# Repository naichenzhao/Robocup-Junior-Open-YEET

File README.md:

**Robocup Junior YEET**

These are the robot designs I created for Robocup Junior Open weight. 

These are my own creations and since I have graduated from the event, anyone rteading this is free to build off of any of my designs. My hope for this is to inspire others to build off of what I haev and use them to create even better concepts for the competition.

If you have any questions or concerns regarding the design, feel free to contact me:
- Twitter: https://twitter.com/N_zhao_
- Discord: https://discord.gg/ySBR4mmBkV

Included in the repo are:
- My 2020 design I planned on using for that year's competition - This is mostly tested but never created
- My 2021 design Which is pureley theoretical. It is a modefied version of the 2020 design built around a 20cm diameter

**2020 Design:**
This is the robot I planned on using for the 2020 competition (Which was cancelled due to covid). Some parts of the robot were tested but it was never completed as production stopped when the competition was cancelled

The specs of the robot are:
- 2x Teensy 4.0
- 1x Teensy 3.5
- 1x Open MV H7 (Omnidirectional mirror)
- 1x Spinning LIDAR
- 1x Bluetooth module
- 1x BNO-055 Accelerometer
- 2x Dribbler
- 2x Directional Kicker (I created models using both slider and geneva methods)
- 32x Photoresistors w/ LEDs (Controlled by 2 multiplexers)
- 12x Buttons w/ LEDs
- 2x IR laser module

**2021 Design:**
This is a robot built for the 2021 competition but since there is a significant chance that the competition will be cancalled, I have decided to thus release all of the robot files. This design is a smaller version built around the 2020 design created around a 20cm diameter instead of a 22 cm diameter

The specs of the robot are:
- 2x Teensy 4.0
- 1x Teensy 4.1
- 1x Open MV H7 (Omnidirectional mirror)
- 1x Spinning LIDAR
- 1x Bluetooth module
- 1x BNO-055 Accelerometer
- 2x Dribbler
- 2x Kicker
- 32x Photoresistors w/ LEDs (Controlled by 2 multiplexers)
- 8x Buttons w/ LEDs (Intead of individual LEDs, I am using a neopixel strip to conserve pins)
- 2x IR laser module

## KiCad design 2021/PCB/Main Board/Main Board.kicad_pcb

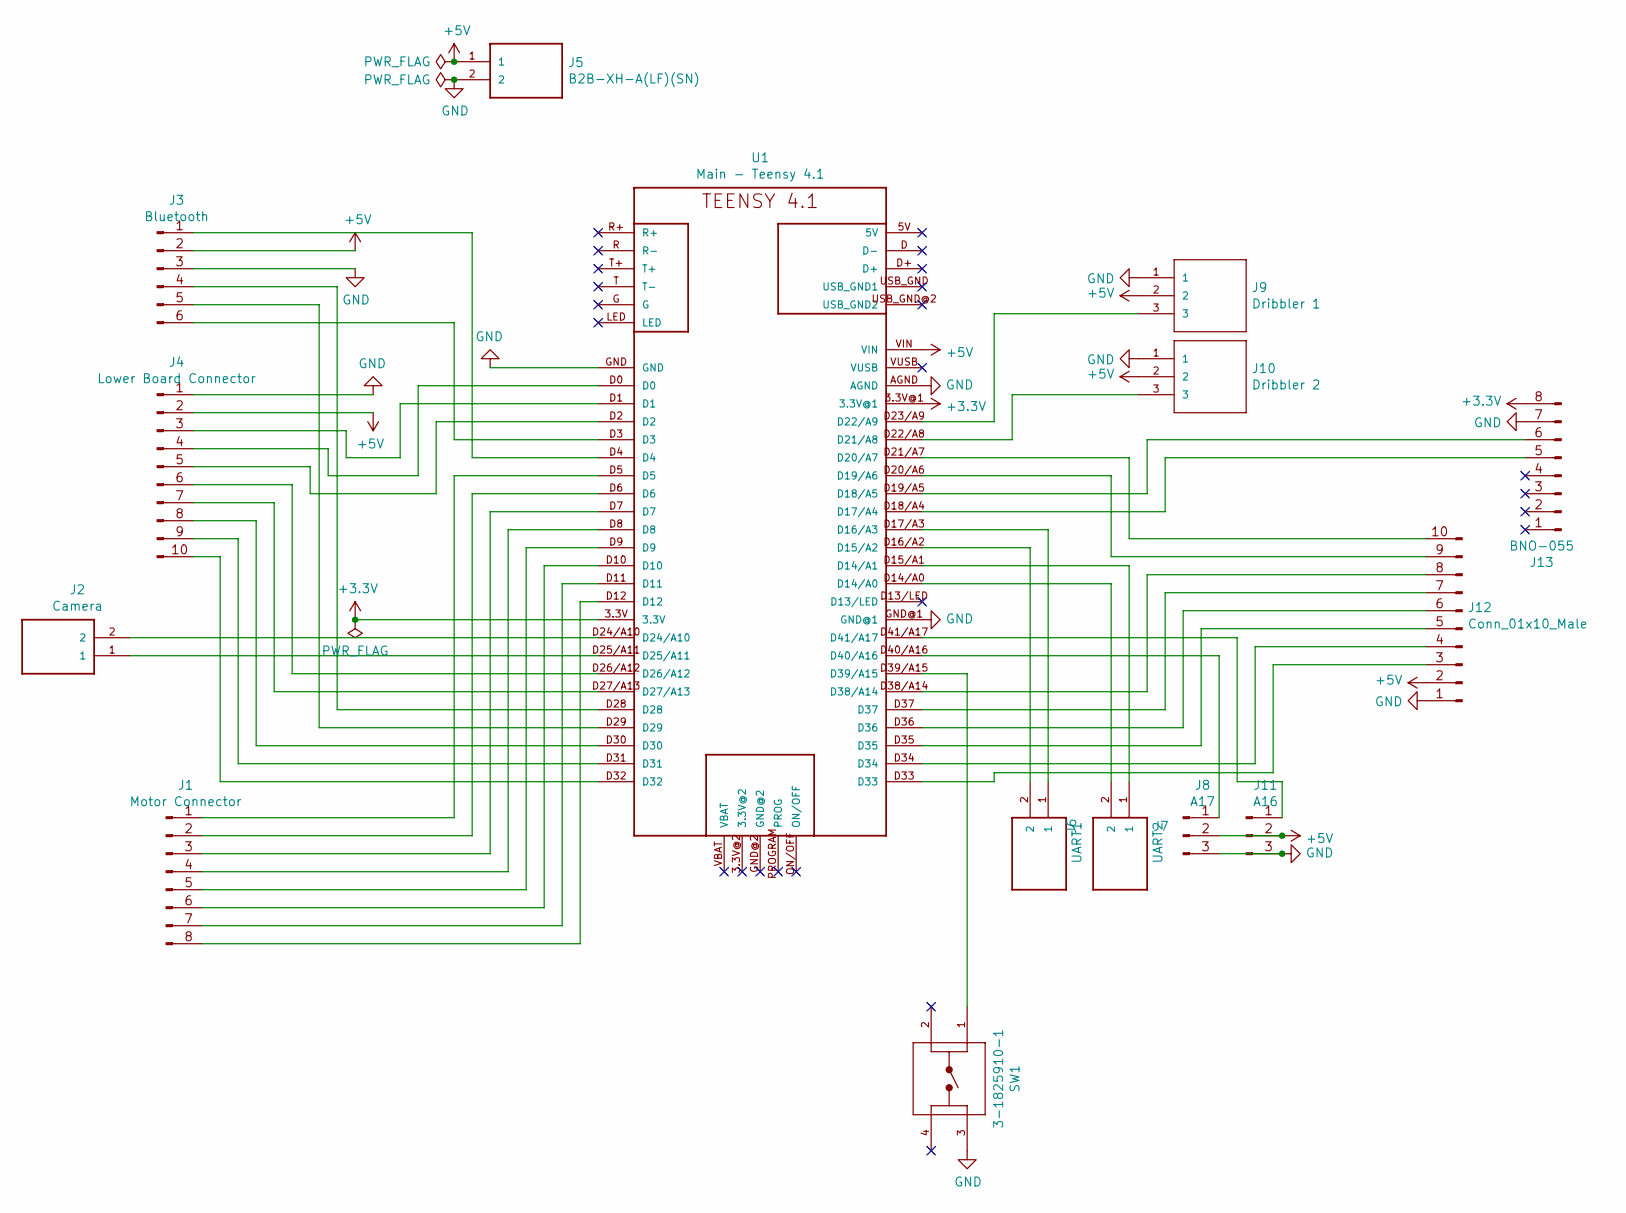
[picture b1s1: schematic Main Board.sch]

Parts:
J1: Motor Connector; Stocko_MKS_1658-6-0-808_1x8_P2.50mm_Vertical
J2: Camera; JST_EH_B2B-EH-A_1x02_P2.50mm_Vertical
J3: Bluetooth; Stocko_MKS_1656-6-0-606_1x6_P2.50mm_Vertical
J4: Lower Board Connector; JST_XH_B10B-XH-AM_1x10_P2.50mm_Vertical
J5: B2B-XH-A(LF)(SN); JST_EH_B2B-EH-A_1x02_P2.50mm_Vertical
J6: UART1; JST_EH_B2B-EH-A_1x02_P2.50mm_Vertical
J7: UART2; JST_EH_B2B-EH-A_1x02_P2.50mm_Vertical
J8: A17; JST_EH_B3B-EH-A_1x03_P2.50mm_Vertical
J9: Dribbler 1; JST_EH_B3B-EH-A_1x03_P2.50mm_Vertical
J10: Dribbler 2; JST_EH_B3B-EH-A_1x03_P2.50mm_Vertical
J11: A16; JST_EH_B3B-EH-A_1x03_P2.50mm_Vertical
J12: Conn_01x10_Male; JST_XH_B10B-XH-AM_1x10_P2.50mm_Vertical
J13: BNO-055; PinHeader_1x08_P2.54mm_Vertical
SW1: 3-1825910-1; TE_3-1825910-1
U1: Main - Teensy 4.1; DEV-16771

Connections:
+3V3: J13.8, U1.3.3V, U1.3.3V@1
+5V: J3.2, J4.2, J5.1, J8.2, J9.2, J10.2, J11.2, J12.2, U1.VIN
GND: J3.3, J4.1, J5.2, J8.3, J9.1, J10.1, J11.3, J12.1, J13.7, SW1.3, U1.AGND, U1.GND, U1.GND@1
unnamed: J1.1, U1.D5
unnamed: J1.2, U1.D6
unnamed: J1.3, U1.D7
unnamed: J1.4, U1.D8
unnamed: J1.5, U1.D9
unnamed: J1.6, U1.D10
unnamed: J1.7, U1.D11
unnamed: J1.8, U1.D12
unnamed: J2.1, U1.D25/A11
unnamed: J2.2, U1.D24/A10
unnamed: J3.1, U1.D4
unnamed: J3.4, U1.D28
unnamed: J3.5, U1.D29
unnamed: J3.6, U1.D3
unnamed: J4.3, U1.D1
unnamed: J4.4, U1.D0
unnamed: J4.5, U1.D2
unnamed: J4.6, U1.D26/A12
unnamed: J4.7, U1.D27/A13
unnamed: J4.8, U1.D30
unnamed: J4.9, U1.D31
unnamed: J4.10, U1.D32
unnamed: J6.1, U1.D17/A3 (D16/A3)
unnamed: J6.2, U1.D16/A2 (D15/A2)
unnamed: J7.1, U1.D15/A1 (D14/A1)
unnamed: J7.2, U1.D14/A0
unnamed: J8.1, U1.D40/A16
unnamed: J9.3, U1.D23/A9 (D22/A9)
unnamed: J10.3, U1.D22/A8 (D21/A8)
unnamed: J11.1, U1.D41/A17
unnamed: J12.3, U1.D33
unnamed: J12.4, U1.D34
unnamed: J12.5, U1.D35
unnamed: J12.6, U1.D36
unnamed: J12.7, U1.D37
unnamed: J12.8, U1.D38/A14
unnamed: J12.9, U1.D20/A6 (D19/A6)
unnamed: J12.10, U1.D21/A7 (D20/A7)
unnamed: J13.5, U1.D18/A4 (D17/A4)
unnamed: J13.6, U1.D19/A5 (D18/A5)
unnamed: SW1.1, U1.D39/A15

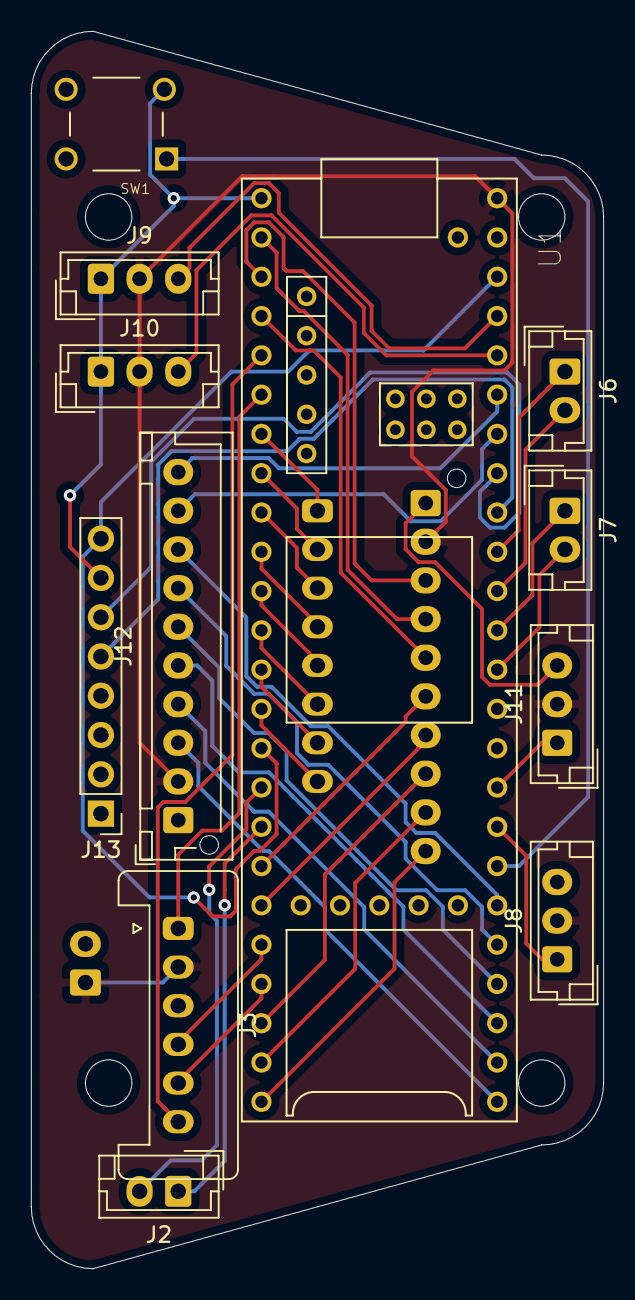
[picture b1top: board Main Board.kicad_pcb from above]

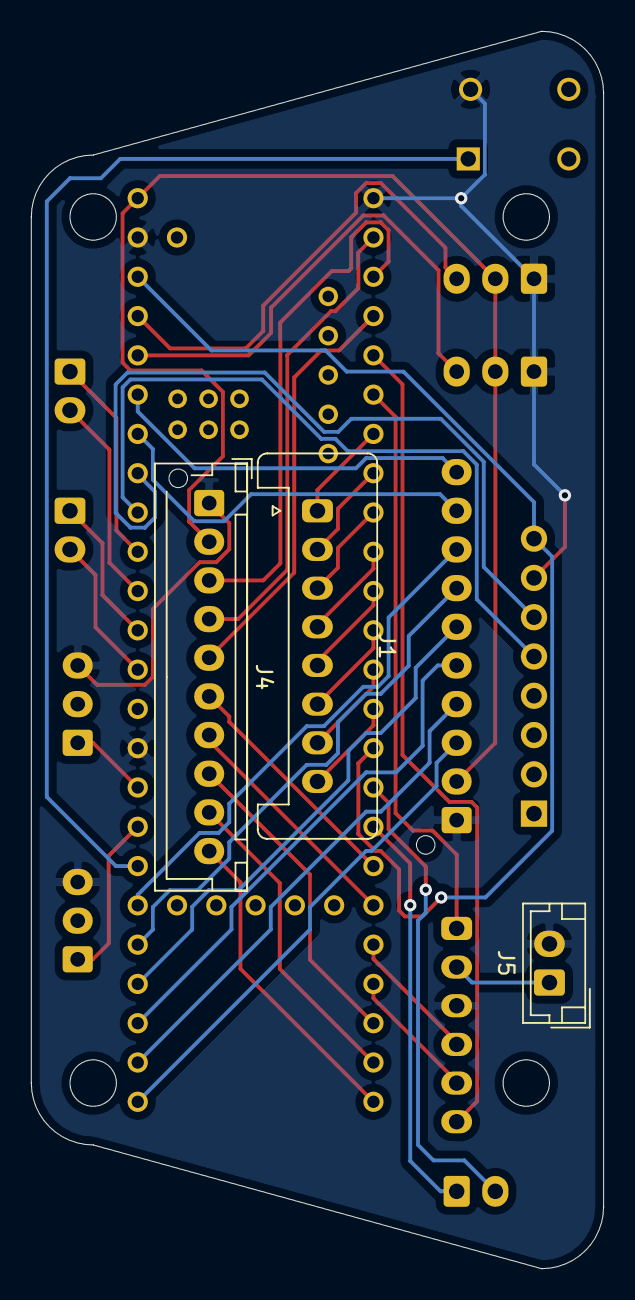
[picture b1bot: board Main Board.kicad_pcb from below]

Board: 2 copper layers, 37.0 x 80.0 mm, 15 parts (3 on the bottom side), 44 nets.

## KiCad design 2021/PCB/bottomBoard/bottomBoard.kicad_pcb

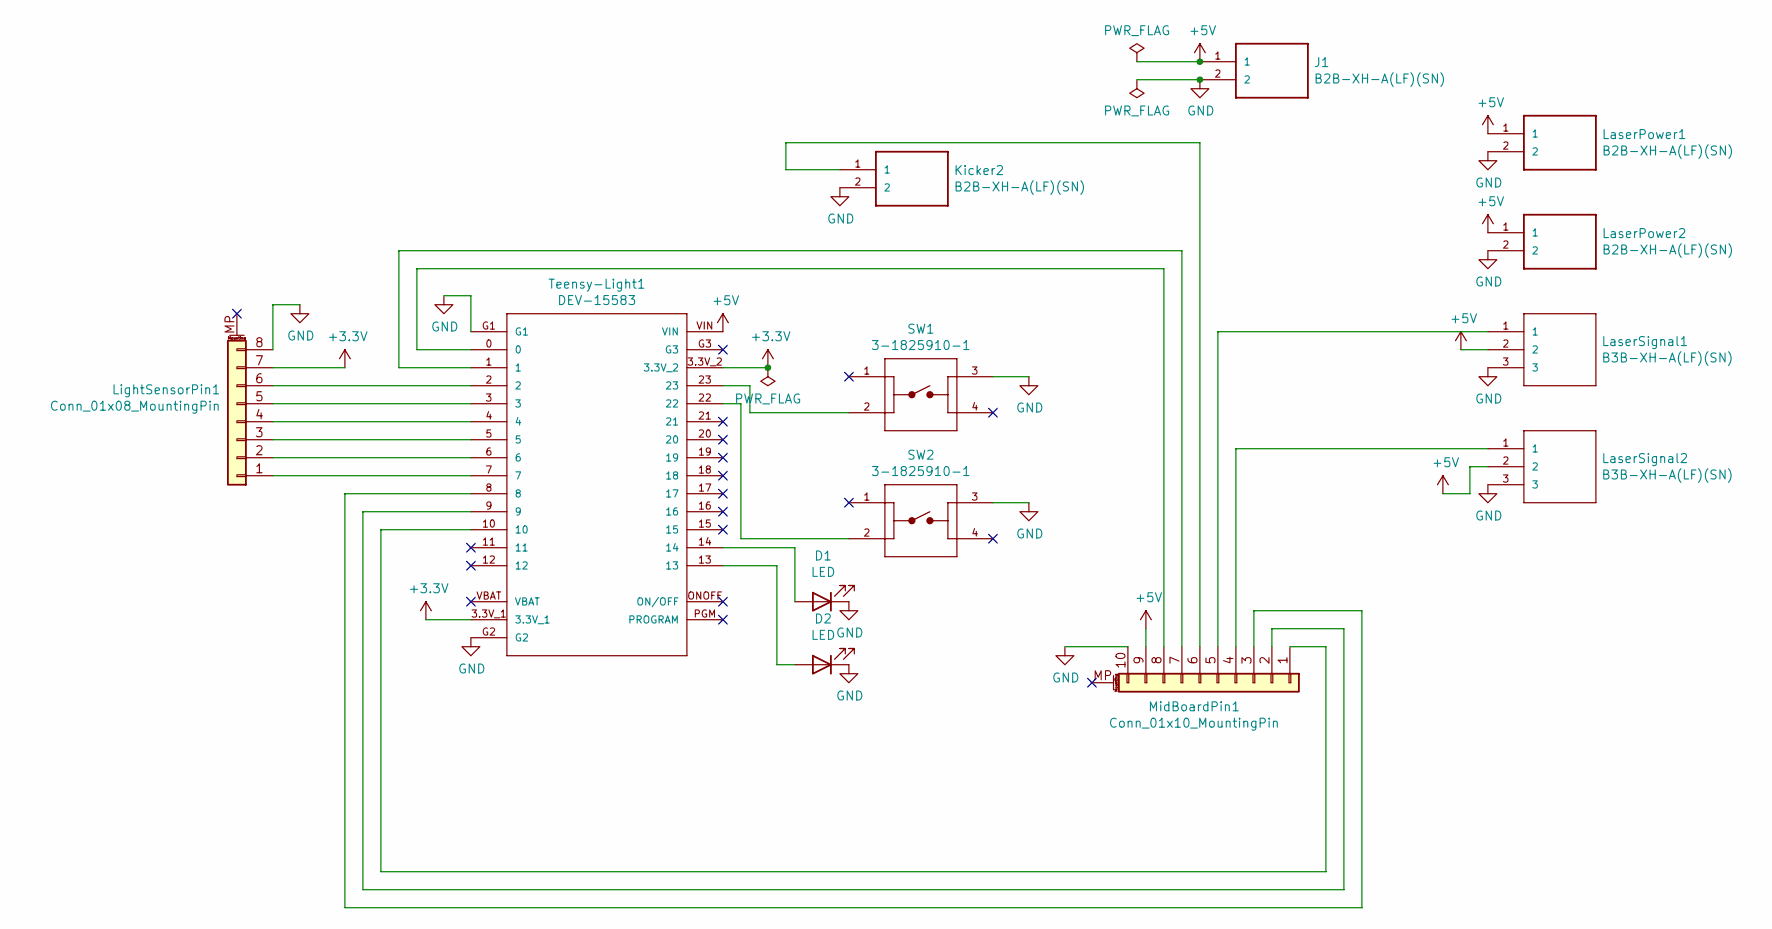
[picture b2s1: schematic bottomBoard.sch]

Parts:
D1, D2: LED; C_1206_3216Metric
J1: B2B-XH-A(LF)(SN); JST_B2B-XH-A(LF)(SN)
Kicker2: B2B-XH-A(LF)(SN); JST_B2B-XH-A(LF)(SN)
LaserPower1, LaserPower2: B2B-XH-A(LF)(SN); JST_B2B-XH-A(LF)(SN)
LaserSignal1, LaserSignal2: B3B-XH-A(LF)(SN); JST_B3B-XH-A(LF)(SN)
LightSensorPin1: Conn_01x08_MountingPin; PinHeader_1x08_P2.54mm_Vertical
MidBoardPin1: Conn_01x10_MountingPin; PinHeader_1x10_P2.54mm_Vertical
SW1, SW2: 3-1825910-1; TE_3-1825910-1
Teensy-Light1: DEV-15583; MODULE_DEV-15583

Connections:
+3V3: LightSensorPin1.7, Teensy-Light1.3.3V_1, Teensy-Light1.3.3V_2
+5V: J1.1, LaserPower1.1, LaserPower2.1, LaserSignal1.2, LaserSignal2.2, MidBoardPin1.9, Teensy-Light1.VIN
GND: D1.1 (K), D2.1 (K), J1.2, Kicker2.2, LaserPower1.2, LaserPower2.2, LaserSignal1.3, LaserSignal2.3, LightSensorPin1.8, MidBoardPin1.10, SW1.3, SW2.3, Teensy-Light1.G1, Teensy-Light1.G2
unnamed: D1.2 (A), Teensy-Light1.14
unnamed: D2.2 (A), Teensy-Light1.13
unnamed: Kicker2.1, MidBoardPin1.6
unnamed: LaserSignal1.1, MidBoardPin1.5
unnamed: LaserSignal2.1, MidBoardPin1.4
unnamed: LightSensorPin1.1, Teensy-Light1.7
unnamed: LightSensorPin1.2, Teensy-Light1.6
unnamed: LightSensorPin1.3, Teensy-Light1.5
unnamed: LightSensorPin1.4, Teensy-Light1.4
unnamed: LightSensorPin1.5, Teensy-Light1.3
unnamed: LightSensorPin1.6, Teensy-Light1.2
unnamed: MidBoardPin1.1, Teensy-Light1.10
unnamed: MidBoardPin1.2, Teensy-Light1.9
unnamed: MidBoardPin1.3, Teensy-Light1.8
unnamed: MidBoardPin1.7, Teensy-Light1.1
unnamed: MidBoardPin1.8, Teensy-Light1.0
unnamed: SW1.2, Teensy-Light1.23
unnamed: SW2.2, Teensy-Light1.22

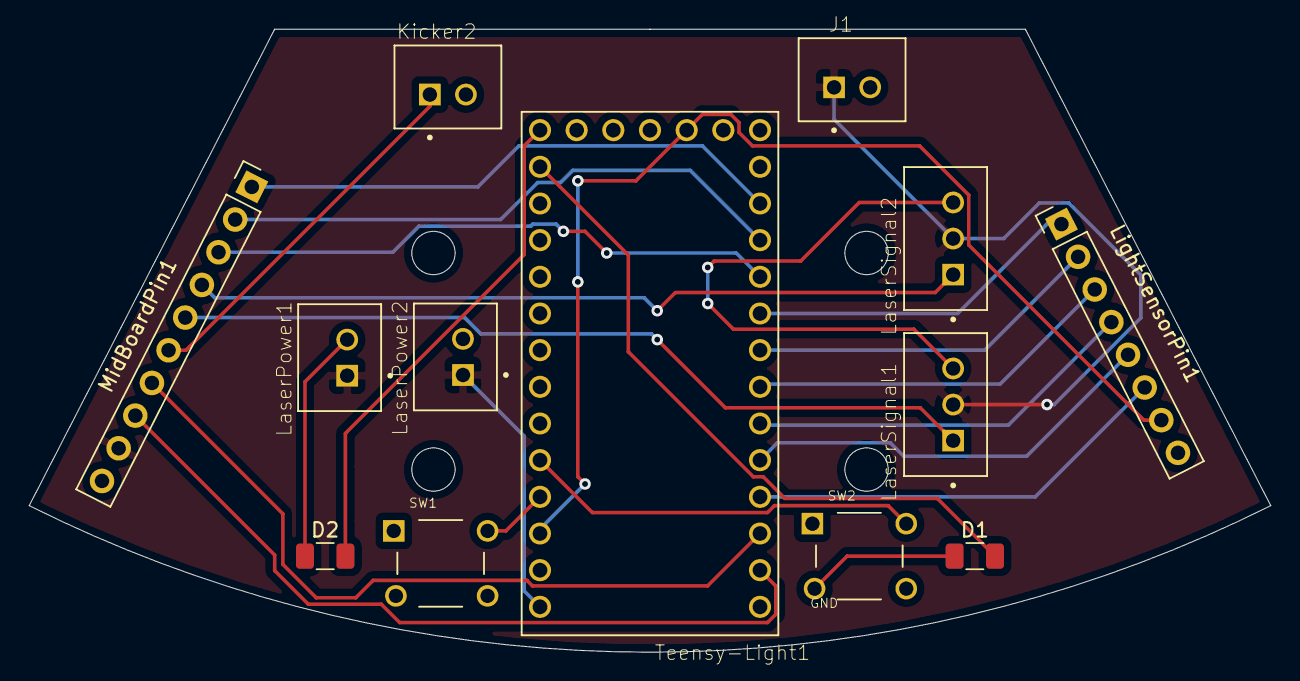
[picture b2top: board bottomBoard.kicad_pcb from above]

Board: 2 copper layers, 86.0 x 43.2 mm, 13 parts (0 on the bottom side), 21 nets.

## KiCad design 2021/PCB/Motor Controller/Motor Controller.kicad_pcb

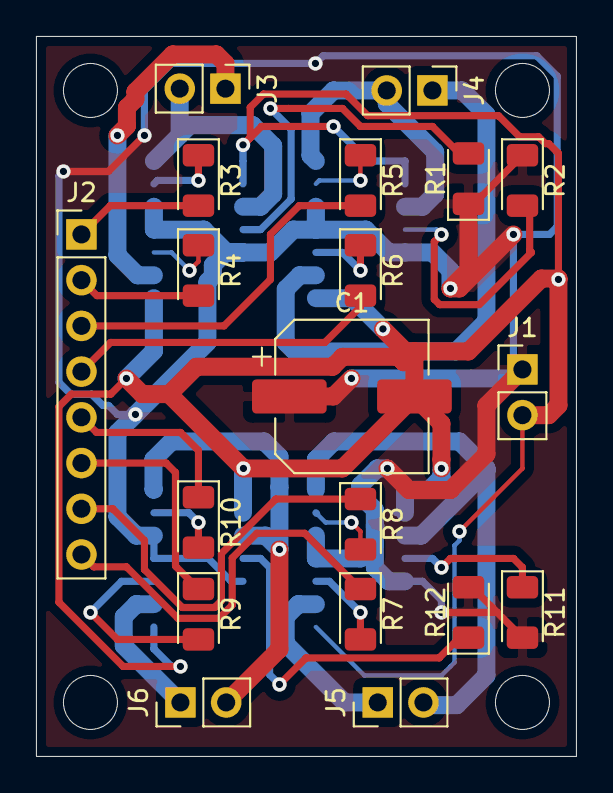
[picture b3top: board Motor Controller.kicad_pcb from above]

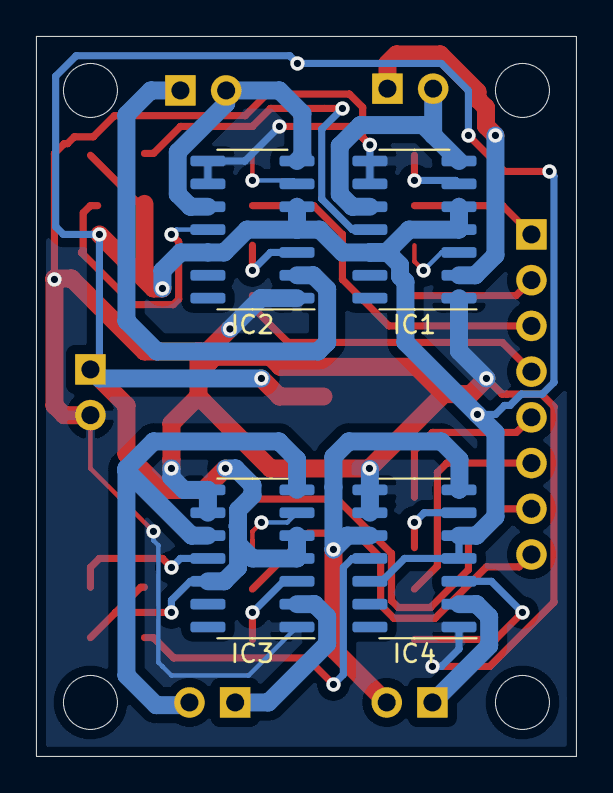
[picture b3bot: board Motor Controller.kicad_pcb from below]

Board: 2 copper layers, 30.0 x 40.0 mm, 23 parts (4 on the bottom side), 30 nets.

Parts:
C1: UUD1V331MNL1GS; CP_Elec_8x11.9
IC1, IC2, IC3, IC4: VNH7070ASTR; SOIC-14_3.9x8.7mm_P1.27mm
J1, J3, J4, J5, J6: Conn_01x02; PinHeader_1x02_P2.54mm_Vertical
J2: Conn_01x08_MountingPin; PinHeader_1x08_P2.54mm_Vertical
R1, R2, R3, R4, R5, R6, R7, R8, R9, R10, R11, R12: R_US; D_1206_3216Metric

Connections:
+12V: C1.1, IC1.4, IC1.5, IC1.12, IC2.4, IC2.5, IC2.12, IC3.4, IC3.5, IC3.12, IC4.4, IC4.5, IC4.12, J1.1, R1.1, R2.1, R11.2, R12.2
GND: C1.2, IC1.1, IC1.8, IC1.9, IC2.1, IC2.8, IC2.9, IC3.1, IC3.8, IC3.9, IC4.1, IC4.8, IC4.9, J1.2
unnamed: IC1.3, R4.1
unnamed: IC1.6, R3.1
unnamed: IC1.7, IC1.10, J3.2
unnamed: IC1.11, R1.2
unnamed: IC1.2, J3.1
unnamed: IC2.3, R6.1
unnamed: IC2.6, R5.1
unnamed: IC2.7, IC2.10, J4.2
unnamed: IC2.11, R2.2
unnamed: IC2.2, J4.1
unnamed: IC3.3, R7.2
unnamed: IC3.6, R8.2
unnamed: IC3.7, IC3.10, J5.2
unnamed: IC3.11, R11.1
unnamed: IC3.2, J5.1
unnamed: IC4.3, R9.2
unnamed: IC4.6, R10.2
unnamed: IC4.7, IC4.10, J6.2
unnamed: IC4.11, R12.1
unnamed: IC4.2, J6.1
unnamed: J2.1, R3.2
unnamed: J2.2, R4.2
unnamed: J2.3, R5.2
unnamed: J2.4, R6.2
unnamed: J2.5, R10.1
unnamed: J2.6, R9.1
unnamed: J2.7, R8.1
unnamed: J2.8, R7.1

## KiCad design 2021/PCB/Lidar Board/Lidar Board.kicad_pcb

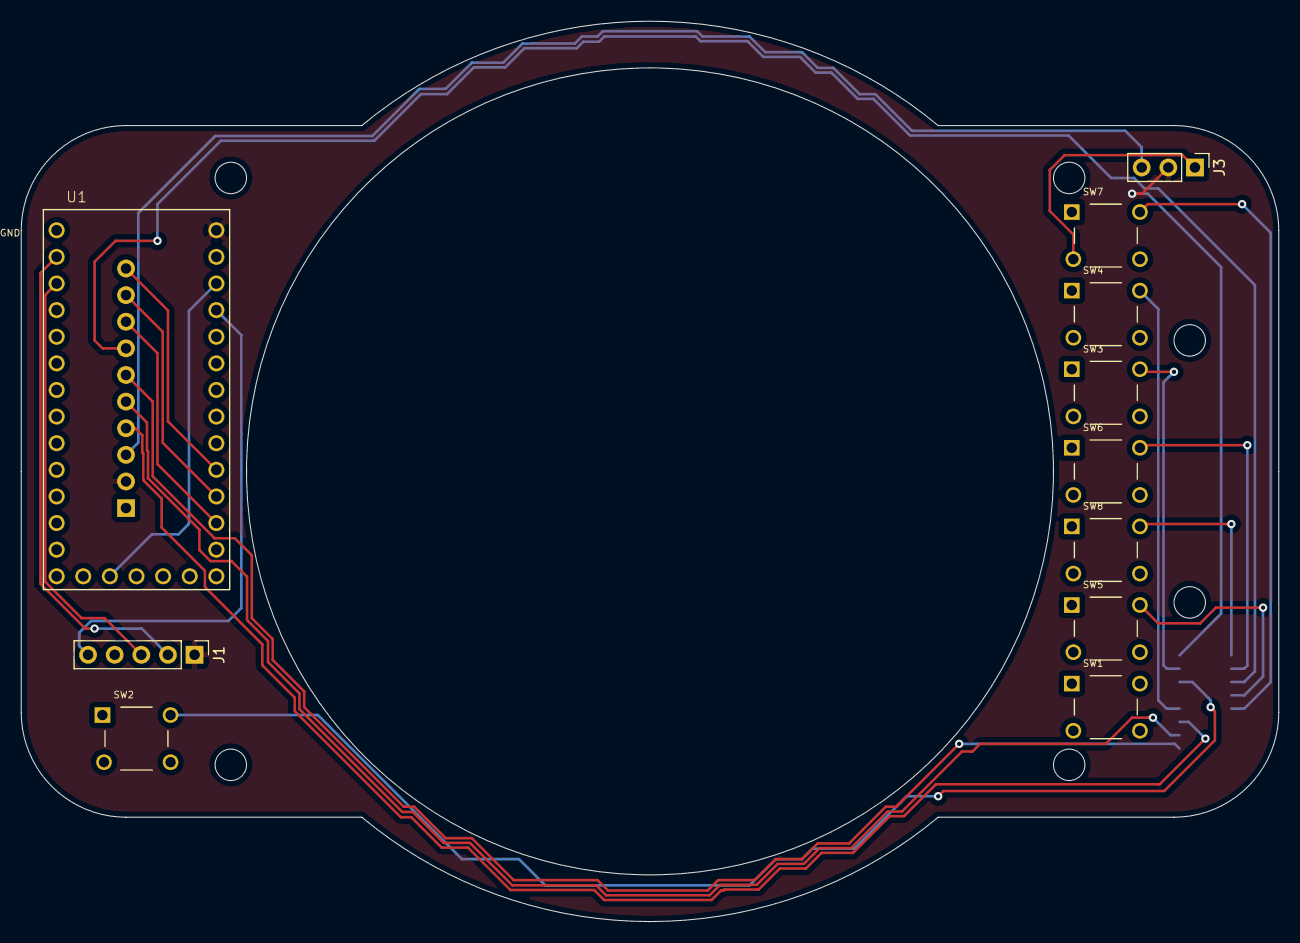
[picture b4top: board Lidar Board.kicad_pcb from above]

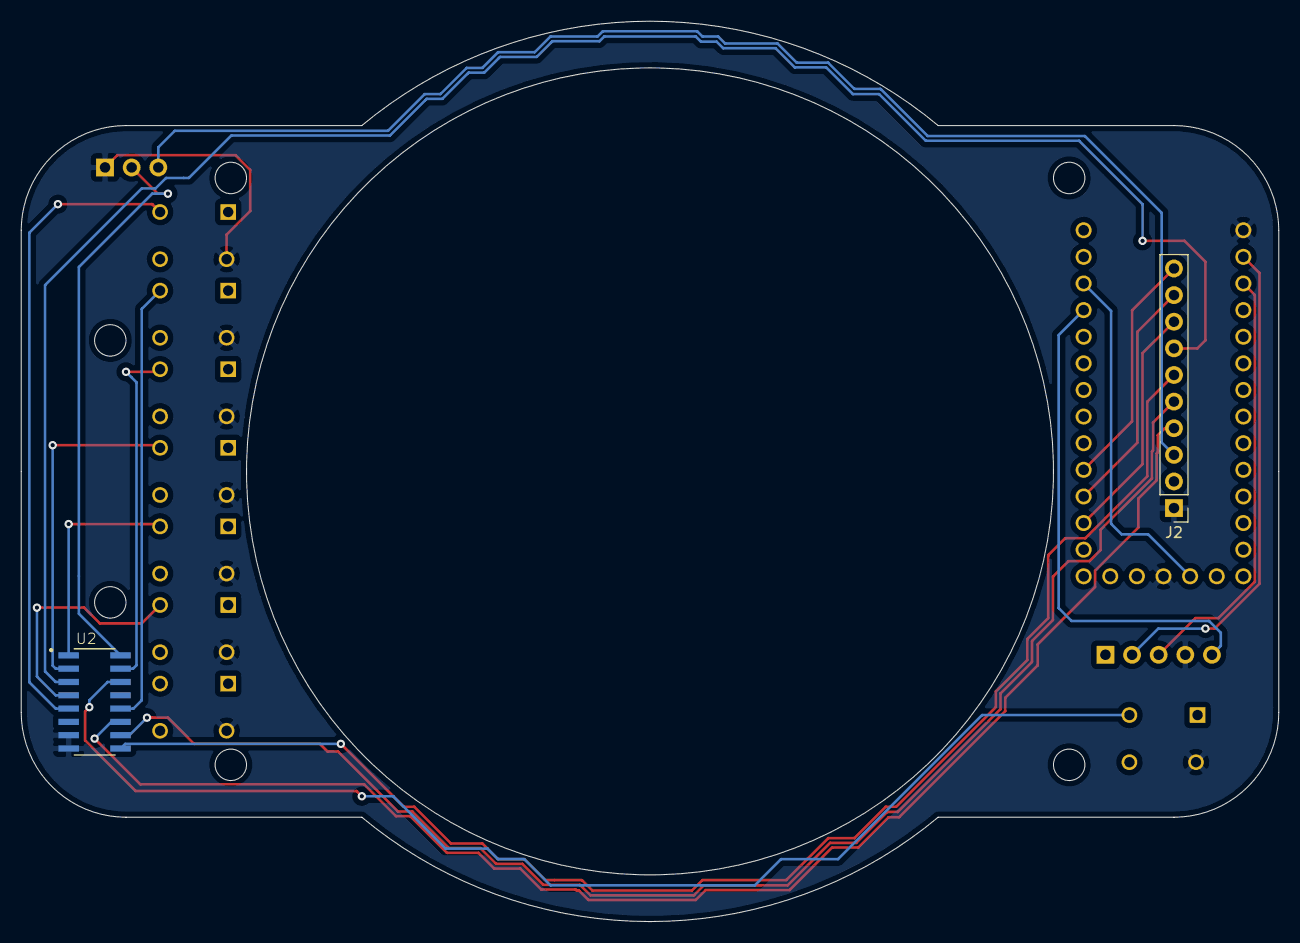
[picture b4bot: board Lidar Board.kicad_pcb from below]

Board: 2 copper layers, 120.0 x 85.9 mm, 13 parts (2 on the bottom side), 21 nets.

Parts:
J1: Conn_01x05_Male; PinHeader_1x05_P2.54mm_Vertical
J2: Conn_01x10_Male; PinHeader_1x10_P2.54mm_Vertical
J3: Conn_01x03_Male; PinHeader_1x03_P2.54mm_Vertical
SW1, SW2, SW3, SW4, SW5, SW6, SW7, SW8: 3-1825910-1; TE_3-1825910-1
U1: DEV-15583; MODULE_DEV-15583
U2: SN74LV4051ADR; SOIC127P600X175-16N

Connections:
+3V3: U1.3.3V_1, U1.3.3V_2
+5V: J1.1, J2.2, J3.2, U1.VIN, U2.16
GND: J1.4, J2.1, J3.1, SW1.3, SW2.3, SW3.3, SW4.3, SW5.3, SW6.3, SW7.3, SW8.3, U1.G1, U1.G2, U2.7, U2.8
unnamed: J1.2, U1.0
unnamed: J1.3, U1.1
unnamed: J1.5, U1.23
unnamed: J2.3, J3.3
unnamed: J2.4, U2.11
unnamed: J2.5, U2.10
unnamed: J2.6, U2.9
unnamed: J2.7, U2.3
unnamed: J2.8, U1.15
unnamed: J2.9, U1.16
unnamed: J2.10, U1.17
unnamed: SW2.2, U2.14
unnamed: SW3.2, U2.15
unnamed: SW4.2, U2.12
unnamed: SW5.2, U2.4
unnamed: SW6.2, U2.2
unnamed: SW7.2, U2.5
unnamed: SW8.2, U2.1

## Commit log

2021-05-24 added files poggers
2021-05-24 added links to readme
2021-05-24 oops more changes lol
2021-11-02 changes readme poggers
2021-11-02 readme spelling
